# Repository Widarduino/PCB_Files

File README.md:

## [Variable Buck Converter(WIP)](./Buck/)

This project involved creating a buck converter which could regulate a 10V power supply to voltage suitable for a breadboard. simulations were done in LTspice and KiCad was used for creating schematics and PCB Layout.

### PCB Revision #1

Currently awaiting second revision, due to high currents causing gate driver IC to fry

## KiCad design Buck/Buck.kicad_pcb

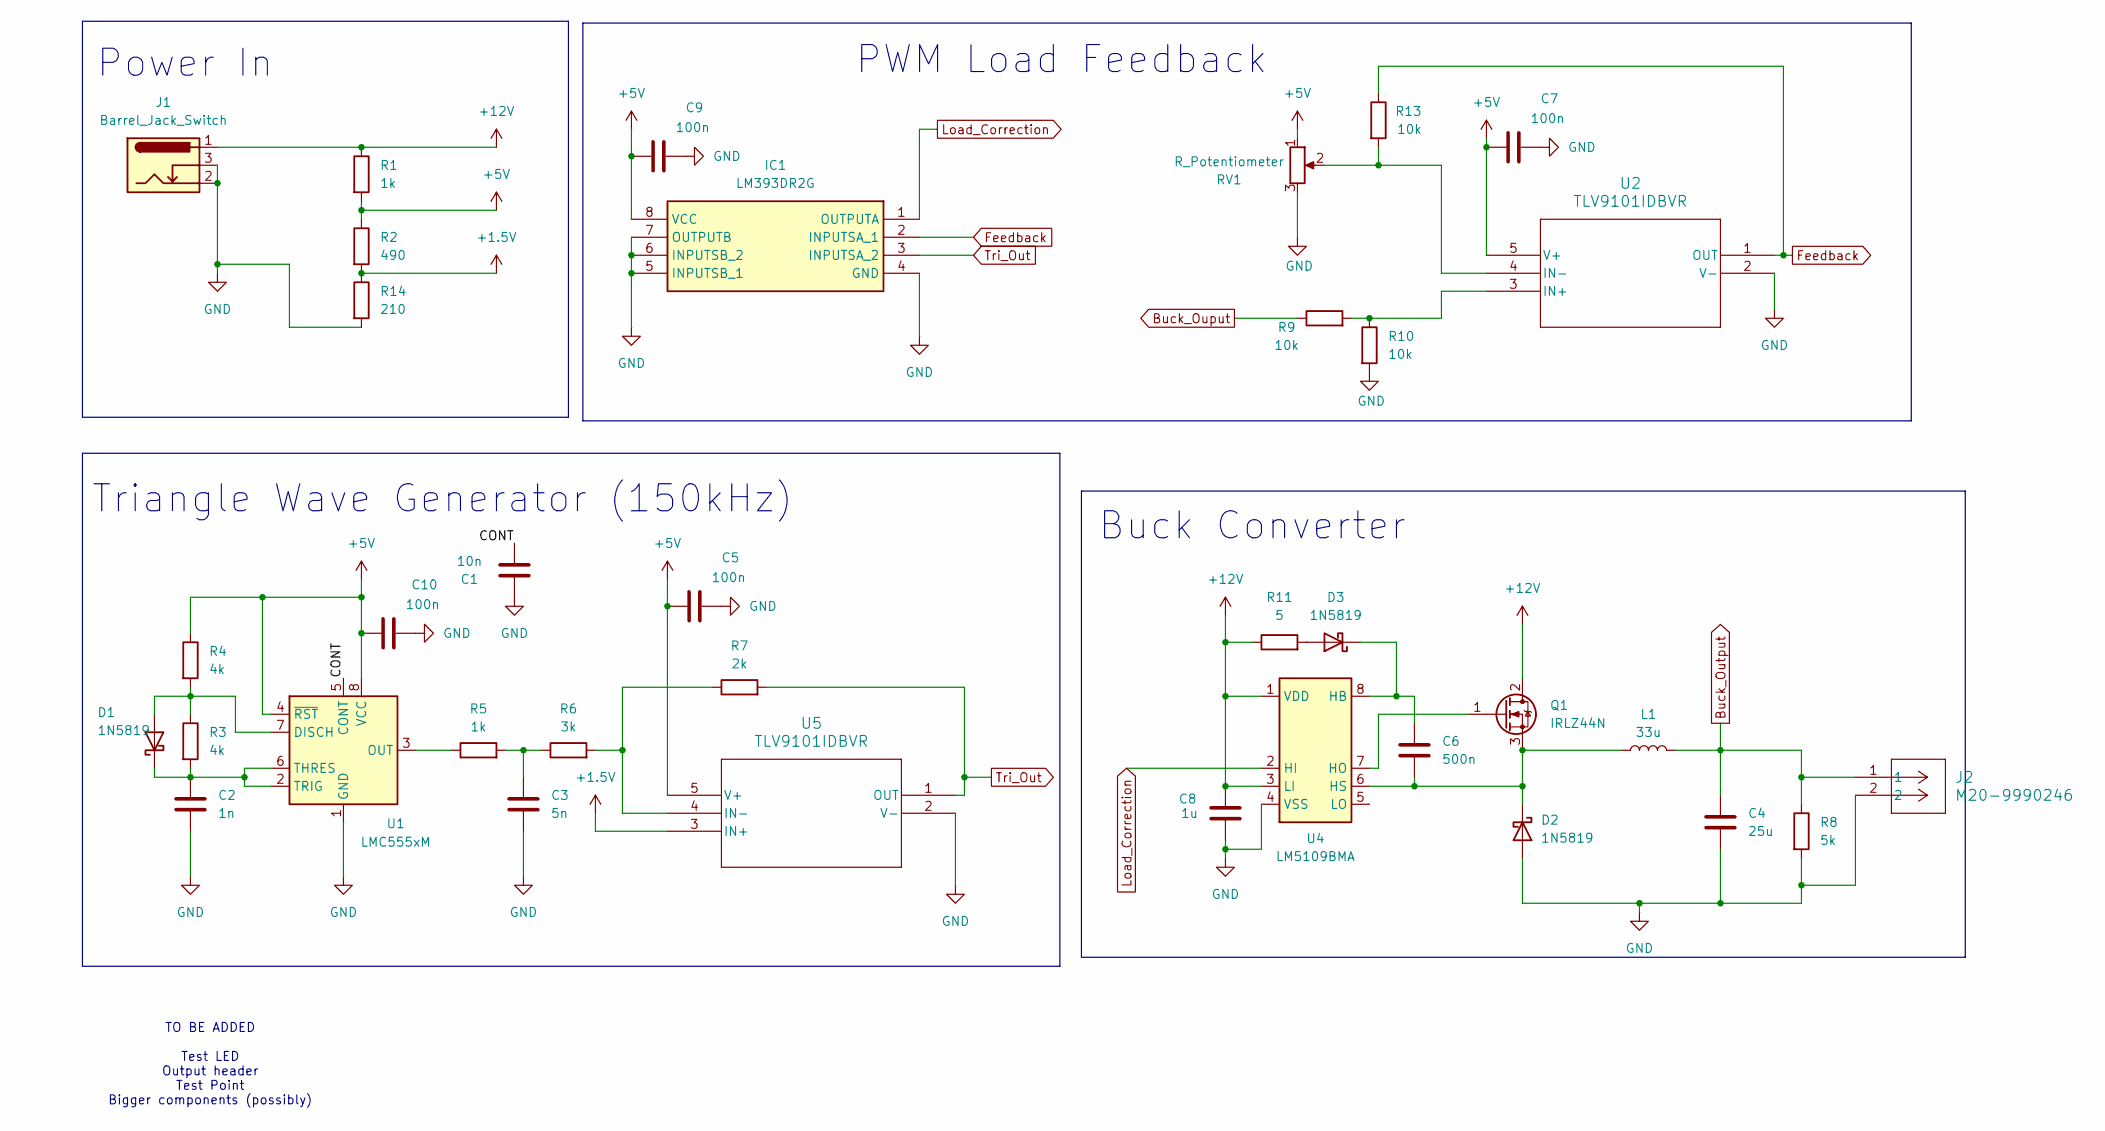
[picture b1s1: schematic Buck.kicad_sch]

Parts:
C1: 10n; C_0201_0603Metric_Pad0.64x0.40mm_HandSolder
C2: 1n; C_0402_1005Metric_Pad0.74x0.62mm_HandSolder
C3: 5n; C_0201_0603Metric_Pad0.64x0.40mm_HandSolder
C4: 25u; C_0805_2012Metric_Pad1.18x1.45mm_HandSolder
C5, C7, C9, C10: 100n; C_0402_1005Metric_Pad0.74x0.62mm_HandSolder
C6: 500n; C_0402_1005Metric_Pad0.74x0.62mm_HandSolder
C8: 1u; C_0402_1005Metric_Pad0.74x0.62mm_HandSolder
D1, D2, D3: 1N5819; D_DO-41_SOD81_P10.16mm_Horizontal
IC1: LM393DR2G; SOIC8_ONS; Manufacturer_Part_Number LM393DR2G; Mouser Part Number 863-LM393DR2G
J1: Barrel_Jack_Switch; CUI_PJ-002A
J2: M20-9990246; CONN2_M20-999_1x2_HRW
L1: 33u; IND_ASPI-4030S-330M-T
Q1: IRLZ44N; TO-220-3_Vertical
R1, R5: 1k; R_0603_1608Metric_Pad0.98x0.95mm_HandSolder
R2: 490; R_0603_1608Metric_Pad0.98x0.95mm_HandSolder
R3, R4: 4k; R_0805_2012Metric_Pad1.20x1.40mm_HandSolder
R6: 3k; R_0402_1005Metric_Pad0.72x0.64mm_HandSolder
R7: 2k; R_0402_1005Metric_Pad0.72x0.64mm_HandSolder
R8: 5k; R_1206_3216Metric_Pad1.30x1.75mm_HandSolder
R9, R10, R13: 10k; R_0402_1005Metric_Pad0.72x0.64mm_HandSolder
R11: 5; R_2512_6332Metric_Pad1.40x3.35mm_HandSolder
R14: 210; R_0402_1005Metric_Pad0.72x0.64mm_HandSolder
RV1: R_Potentiometer; ST-32
U1: LMC555xM; SOIC-8_3.9x4.9mm_P1.27mm
U2, U5: TLV9101IDBVR; DBV0005A_TEX
U4: LM5109BMA; SOIC-8_3.9x4.9mm_P1.27mm

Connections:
+1.5V: R2.2, R14.1, U5.3 (IN+)
+5V: C5.1, C7.1, C9.1, C10.1, IC1.8 (VCC), R1.2, R2.1, R4.1, RV1.1, U1.4 (~RST), U1.8 (VCC), U2.5 (V+), U5.5 (V+)
+12V: C8.2, J1.1, Q1.2 (D), R1.1, R11.1, U4.1 (VDD), U4.3 (LI)
/CONT: C1.1, U1.5 (CONT)
Buck_Ouput: R9.1
Buck_Output: C4.1, J2.1, L1.2, R8.1
Feedback: IC1.2 (INPUTSA_1), R13.1, U2.1 (OUT)
GND: C1.2, C2.2, C3.2, C4.2, C5.2, C7.2, C8.1, C9.2, C10.2, D2.2 (A), IC1.4 (GND), IC1.5 (INPUTSB_1), IC1.6 (INPUTSB_2), IC1.7 (OUTPUTB), J1.2, J1.3, J2.2, R8.2, R10.2, R14.2, RV1.3, U1.1 (GND), U2.2 (V-), U4.4 (VSS), U5.2 (V-)
Load_Correction: IC1.1 (OUTPUTA), U4.2 (HI)
unnamed: C3.1, R5.2, R6.1
unnamed: D1.2 (A), R3.1, R4.2, U1.7 (DISCH)
unnamed: C2.1, D1.1 (K), R3.2, U1.2 (TRIG), U1.6 (THRES)
unnamed: C6.2, D2.1 (K), L1.1, Q1.3 (S), U4.6 (HS)
unnamed: D3.2 (A), R11.2
unnamed: C6.1, D3.1 (K), U4.8 (HB)
unnamed: Q1.1 (G), U4.7 (HO)
unnamed: R5.1, U1.3 (OUT)
unnamed: R9.2, R10.1, U2.3 (IN+)
unnamed: R13.2, RV1.2, U2.4 (IN-)
unnamed: R6.2, R7.1, U5.4 (IN-)
Tri_Out: IC1.3 (INPUTSA_2), R7.2, U5.1 (OUT)

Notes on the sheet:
Triangle Wave Generator (150kHz)
Buck Converter
PWM Load Feedback
TO BE ADDED Test LED Output header Test Point Bigger components (possibly)
Power In

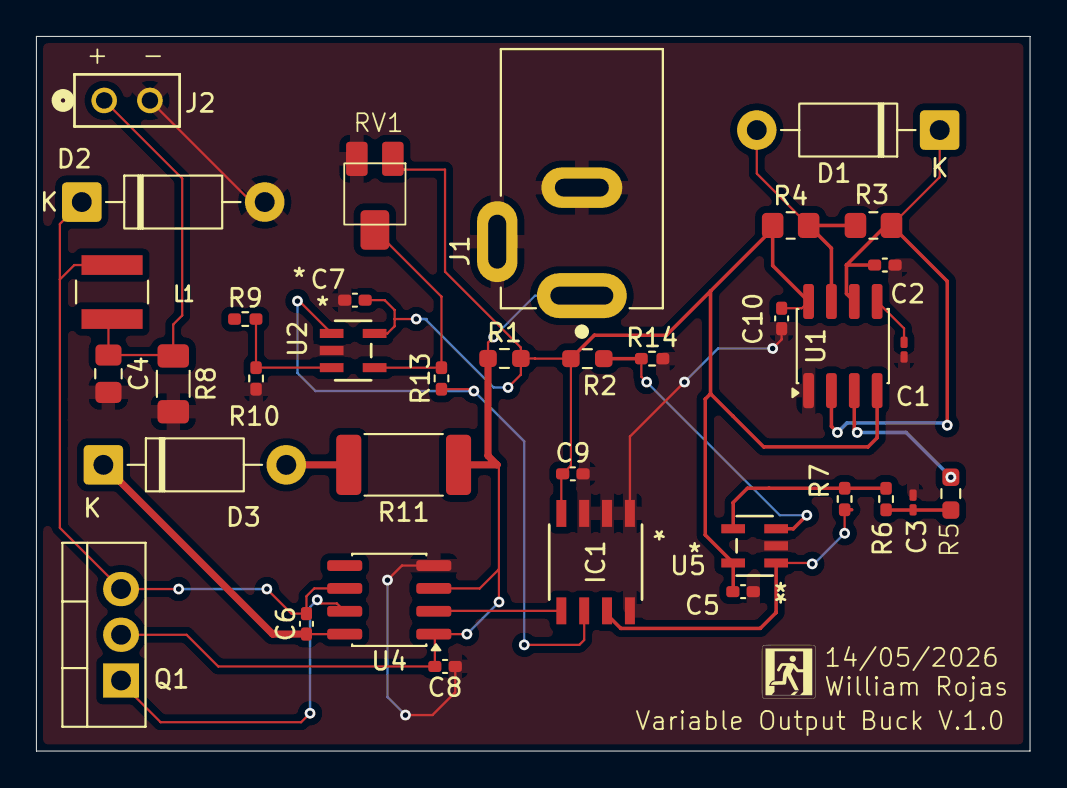
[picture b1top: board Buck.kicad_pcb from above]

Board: 2 copper layers, 55.2 x 39.7 mm, 36 parts (0 on the bottom side), 20 nets.

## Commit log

2026-05-26 Readme test
